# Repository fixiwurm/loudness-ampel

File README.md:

# loudness-ampel
This is the Documentation for a small kit for building a loudness ample. Have Fun!

# Firmware
The firmware is written in Arduino Code, with the help of the MicroCore board packet from McuDude (https://github.com/MCUdude/MicroCore) the code uses around 1010Byte of storage, so it´s completly filled.

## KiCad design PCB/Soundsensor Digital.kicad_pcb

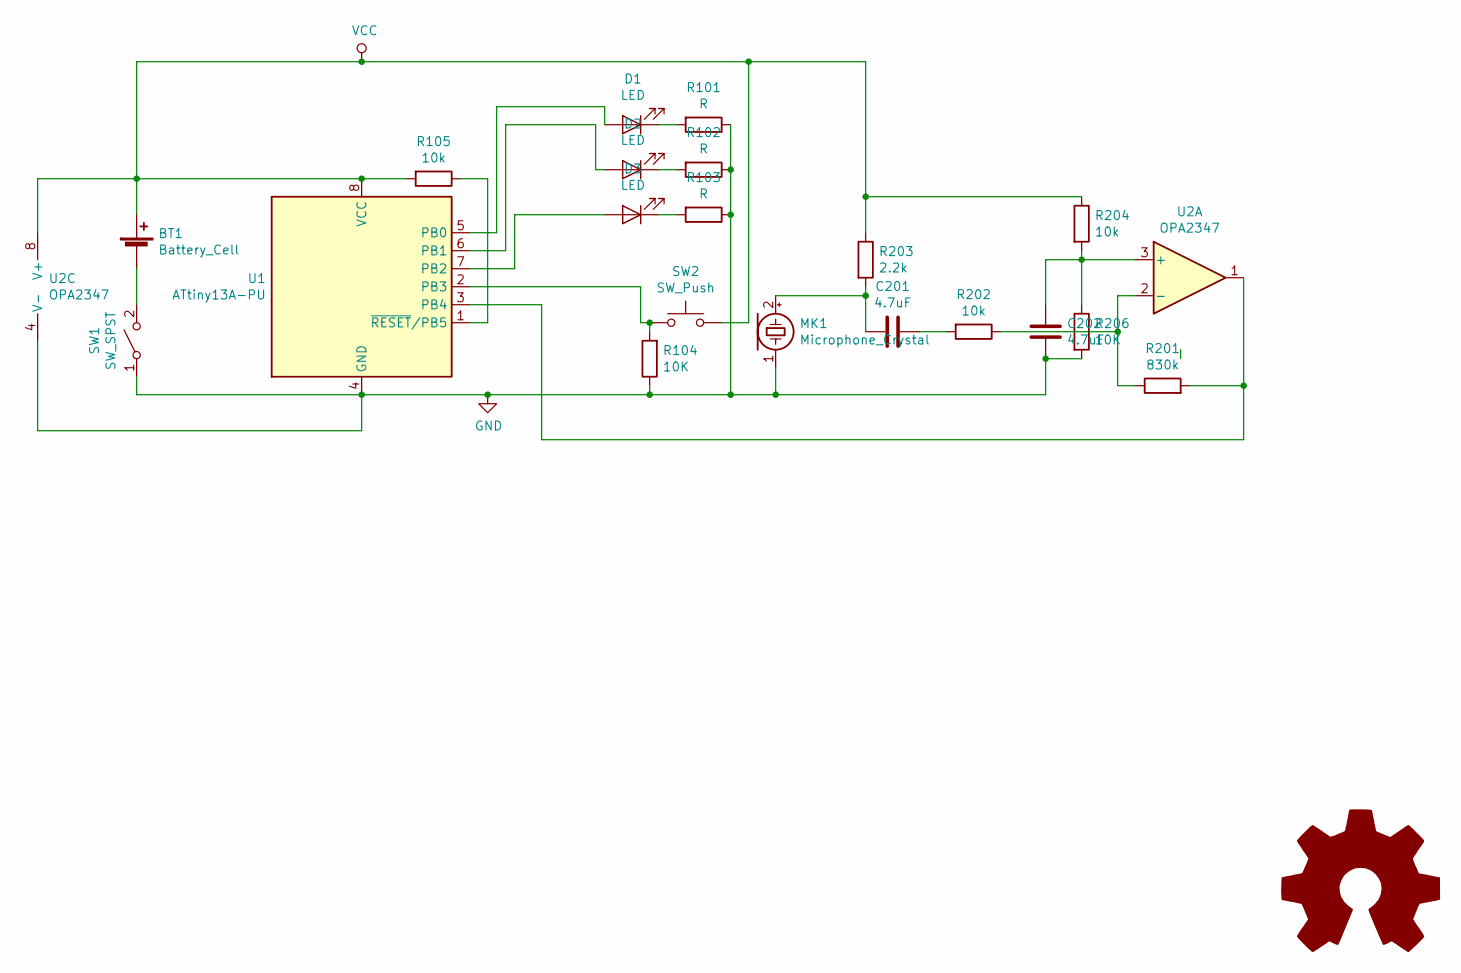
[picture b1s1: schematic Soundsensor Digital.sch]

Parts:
BT1: Battery_Cell; BatteryHolder_Keystone_103_1x20mm
C201, C202: 4.7uF; C_Disc_D6.0mm_W2.5mm_P5.00mm
D1, D2, D3: LED; LED_D5.0mm
MK1: Microphone_Crystal; MICRO_9_7
R101, R102, R103: R; R_Axial_DIN0207_L6.3mm_D2.5mm_P10.16mm_Horizontal
R104, R206: 10K; R_Axial_DIN0207_L6.3mm_D2.5mm_P10.16mm_Horizontal
R105, R202, R204: 10k; R_Axial_DIN0207_L6.3mm_D2.5mm_P10.16mm_Horizontal
R201: 830k; R_Axial_DIN0207_L6.3mm_D2.5mm_P10.16mm_Horizontal
R203: 2.2k; R_Axial_DIN0207_L6.3mm_D2.5mm_P10.16mm_Horizontal
SW1: SW_SPST; SW_Slide_1P2T_CK_OS102011MS2Q
SW2: SW_Push; SW_PUSH_6mm
U1: ATtiny13A-PU; DIP-8_W7.62mm
U2: OPA2347; SO-8

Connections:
GND: C202.2, MK1.1 (-), R101.1, R102.1, R103.1, R104.1, R206.2, SW1.1 (A), U1.4 (GND), U2.4 (V-)
unnamed: BT1.2 (-), SW1.2 (B)
unnamed: C201.1, R202.2
unnamed: C201.2, MK1.2 (+), R203.2
unnamed: C202.1, R204.2, R206.1, U2.3 (+)
unnamed: D1.1 (K), R101.2
unnamed: D1.2 (A), U1.5 (PB0)
unnamed: D2.1 (K), R102.2
unnamed: D2.2 (A), U1.6 (PB1)
unnamed: D3.1 (K), R103.2
unnamed: D3.2 (A), U1.7 (PB2)
unnamed: R104.2, SW2.1, U1.2 (PB3)
unnamed: R105.1, U1.1 (~RESET~/PB5)
unnamed: R201.1, R202.1, U2.2 (-)
unnamed: R201.2, U1.3 (PB4), U2.1
VCC: BT1.1 (+), R105.2, R203.1, R204.1, SW2.2, U1.8 (VCC), U2.8 (V+)

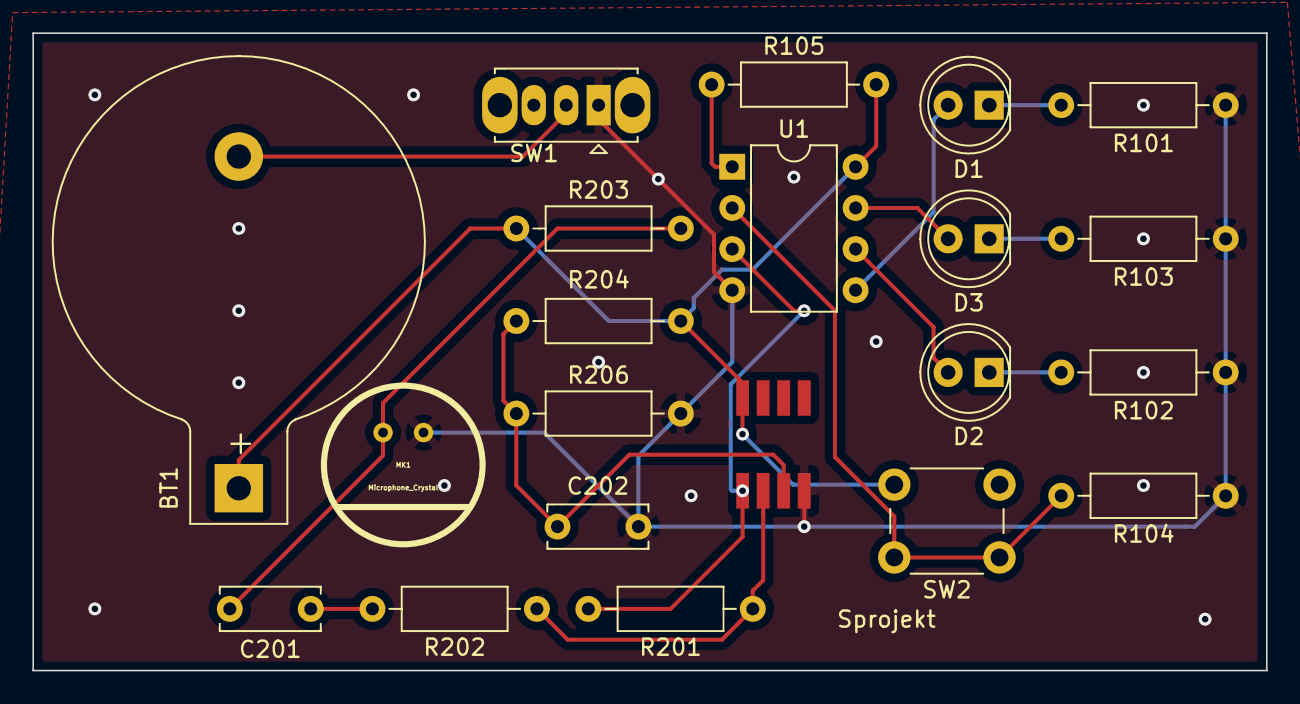
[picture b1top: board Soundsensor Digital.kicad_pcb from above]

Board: 2 copper layers, 76.2 x 39.4 mm, 21 parts (0 on the bottom side), 16 nets.
